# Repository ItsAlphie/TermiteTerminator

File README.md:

# Termite Terminator
For a more in-depth dive into the working and development of this project, we refer to the paper also available in this repository. Below is brief summary on how to set up the game yourself.

## The game
The player manages a coin budget and uses a spell 3 types of tangible towers to face off waves of ants attempting to pass by and eat your picknick. There is a heavy hitting tower with a long cooldown, a tower with a continuisly hitting but low damage laser and a tower that shoots as fast as the player presses its button. Additionally, there is a Freeze spell to hold enemies in place for a few seconds. The ants get increasingly stronger and come in larger groups, but the more enemies are held back, the more coins you earn for more defenses.
[🎥 Watch a demo video on YouTube](https://youtu.be/97M0W15unRk)

## Credits
Both repositories below have been used as a foundation for the python script used for the marker and gesture detection:
* OpenCV Marker Detection: https://github.com/KhairulIzwan/ArUco-markers-with-OpenCV-and-Python
* OpenCV Gesture Detection: https://github.com/kinivi/hand-gesture-recognition-mediapipe

## Setup Instruction
The following instructions are open to adjustments, if the operator deems themselves worthy and knowleadgable enough to customize the setup. But for the others, these next few sections explain how to duplicate our specific setup rather than reconfigure everything.

### Software requirements
Unity Version:
- 2022.3.49f1

python libraries: (Python 3.9 works)
- opencv-contrib-python==4.6.0.66
- imutils
- tensorflow
- mediapipe

### Wireless Connection
#### Background Information
UDP is used to communicate between the main processing computer running the Unity and camera vision, and a set of ESP8266 microcontrollers processing and controlling everything concerning the individual towers.

During the design procedure, hardcoded IP's are used to easily indentify towers and communicate with them accordingly. To set up the wireless network we rely on a mobile hotspot from a modern phone, with a preset 255.255.255.0 subnetmask.

#### Configuration
Following table shows all IP-addresses used:
Device/Service | IP | Use
--- | --- | ---
Towers | 192.168.24.TowerID | Send "b" for boosts, receive "k" and "r" to control servo
Unity (For Towers)| 192.168.24.60 | Receive "b" for boosts and identify tower, send "k" and "r" to selected towers
Unity (For Camera)| 127.0.0.1 | Unity listens to this IP, to locate and place the towers and spells within the playing field

The easiest way to set this network up on new devices is duplicate the original network. Specifically, the network name should be "Galaxy S22A88A" and its password should be "uzjw7402". It is also essential to turn off roaming and internet sevices on the mobile phone, to avoid any external DHCP server to set IP's rendering them unable to be overwritten. Next, the IP of the main computer should be set to match the one in the table above.

### Camera Vision & Towers
This part of the setup refers to the physical configuration. The fundamentals come down to a TV being laid flat on a table (projector would work, but the shadows mess with the gesture recognition) with a camera of any sort hanging above it. Ideally, the camera hangs straight above the center of the screen. 

Within Unity, more specifically in scene "Wave1" in the "LevelManager" the setup can be calibrated. Under the TowerSpawner script skewFactorX, skewFactorY, skewFactorXX, skewFactorYY and heightLimit can be adjusted to conform to the height of the camera, causing a paralax error.

As for the towers, they work on 9V batteries. So, these batteries have to be connected, after which the pins from the connector have to be put in the correct pinheader. The program on the microcontrollers should still be programmed and continue sending and receiving data as normal. As for the recognition of the towers, original aRuCo markers are used with towers ranging from 1 to 7 and the corners of the TV being 21, 22 and 23.

### Start the Game
After you managed to follow all the instruction above, you can now finally launch the game. Simply follow the next few steps to start everything up:
* launch the Unity game
* go to /TermiteTerminator/Python/Gestures/ and launch the python Camera Vision script combinedScripts.py
* make sure to place the three corner markers on your play area
* start the unity game

With this, the script should be sending all required information to the Unity game. Have fun!

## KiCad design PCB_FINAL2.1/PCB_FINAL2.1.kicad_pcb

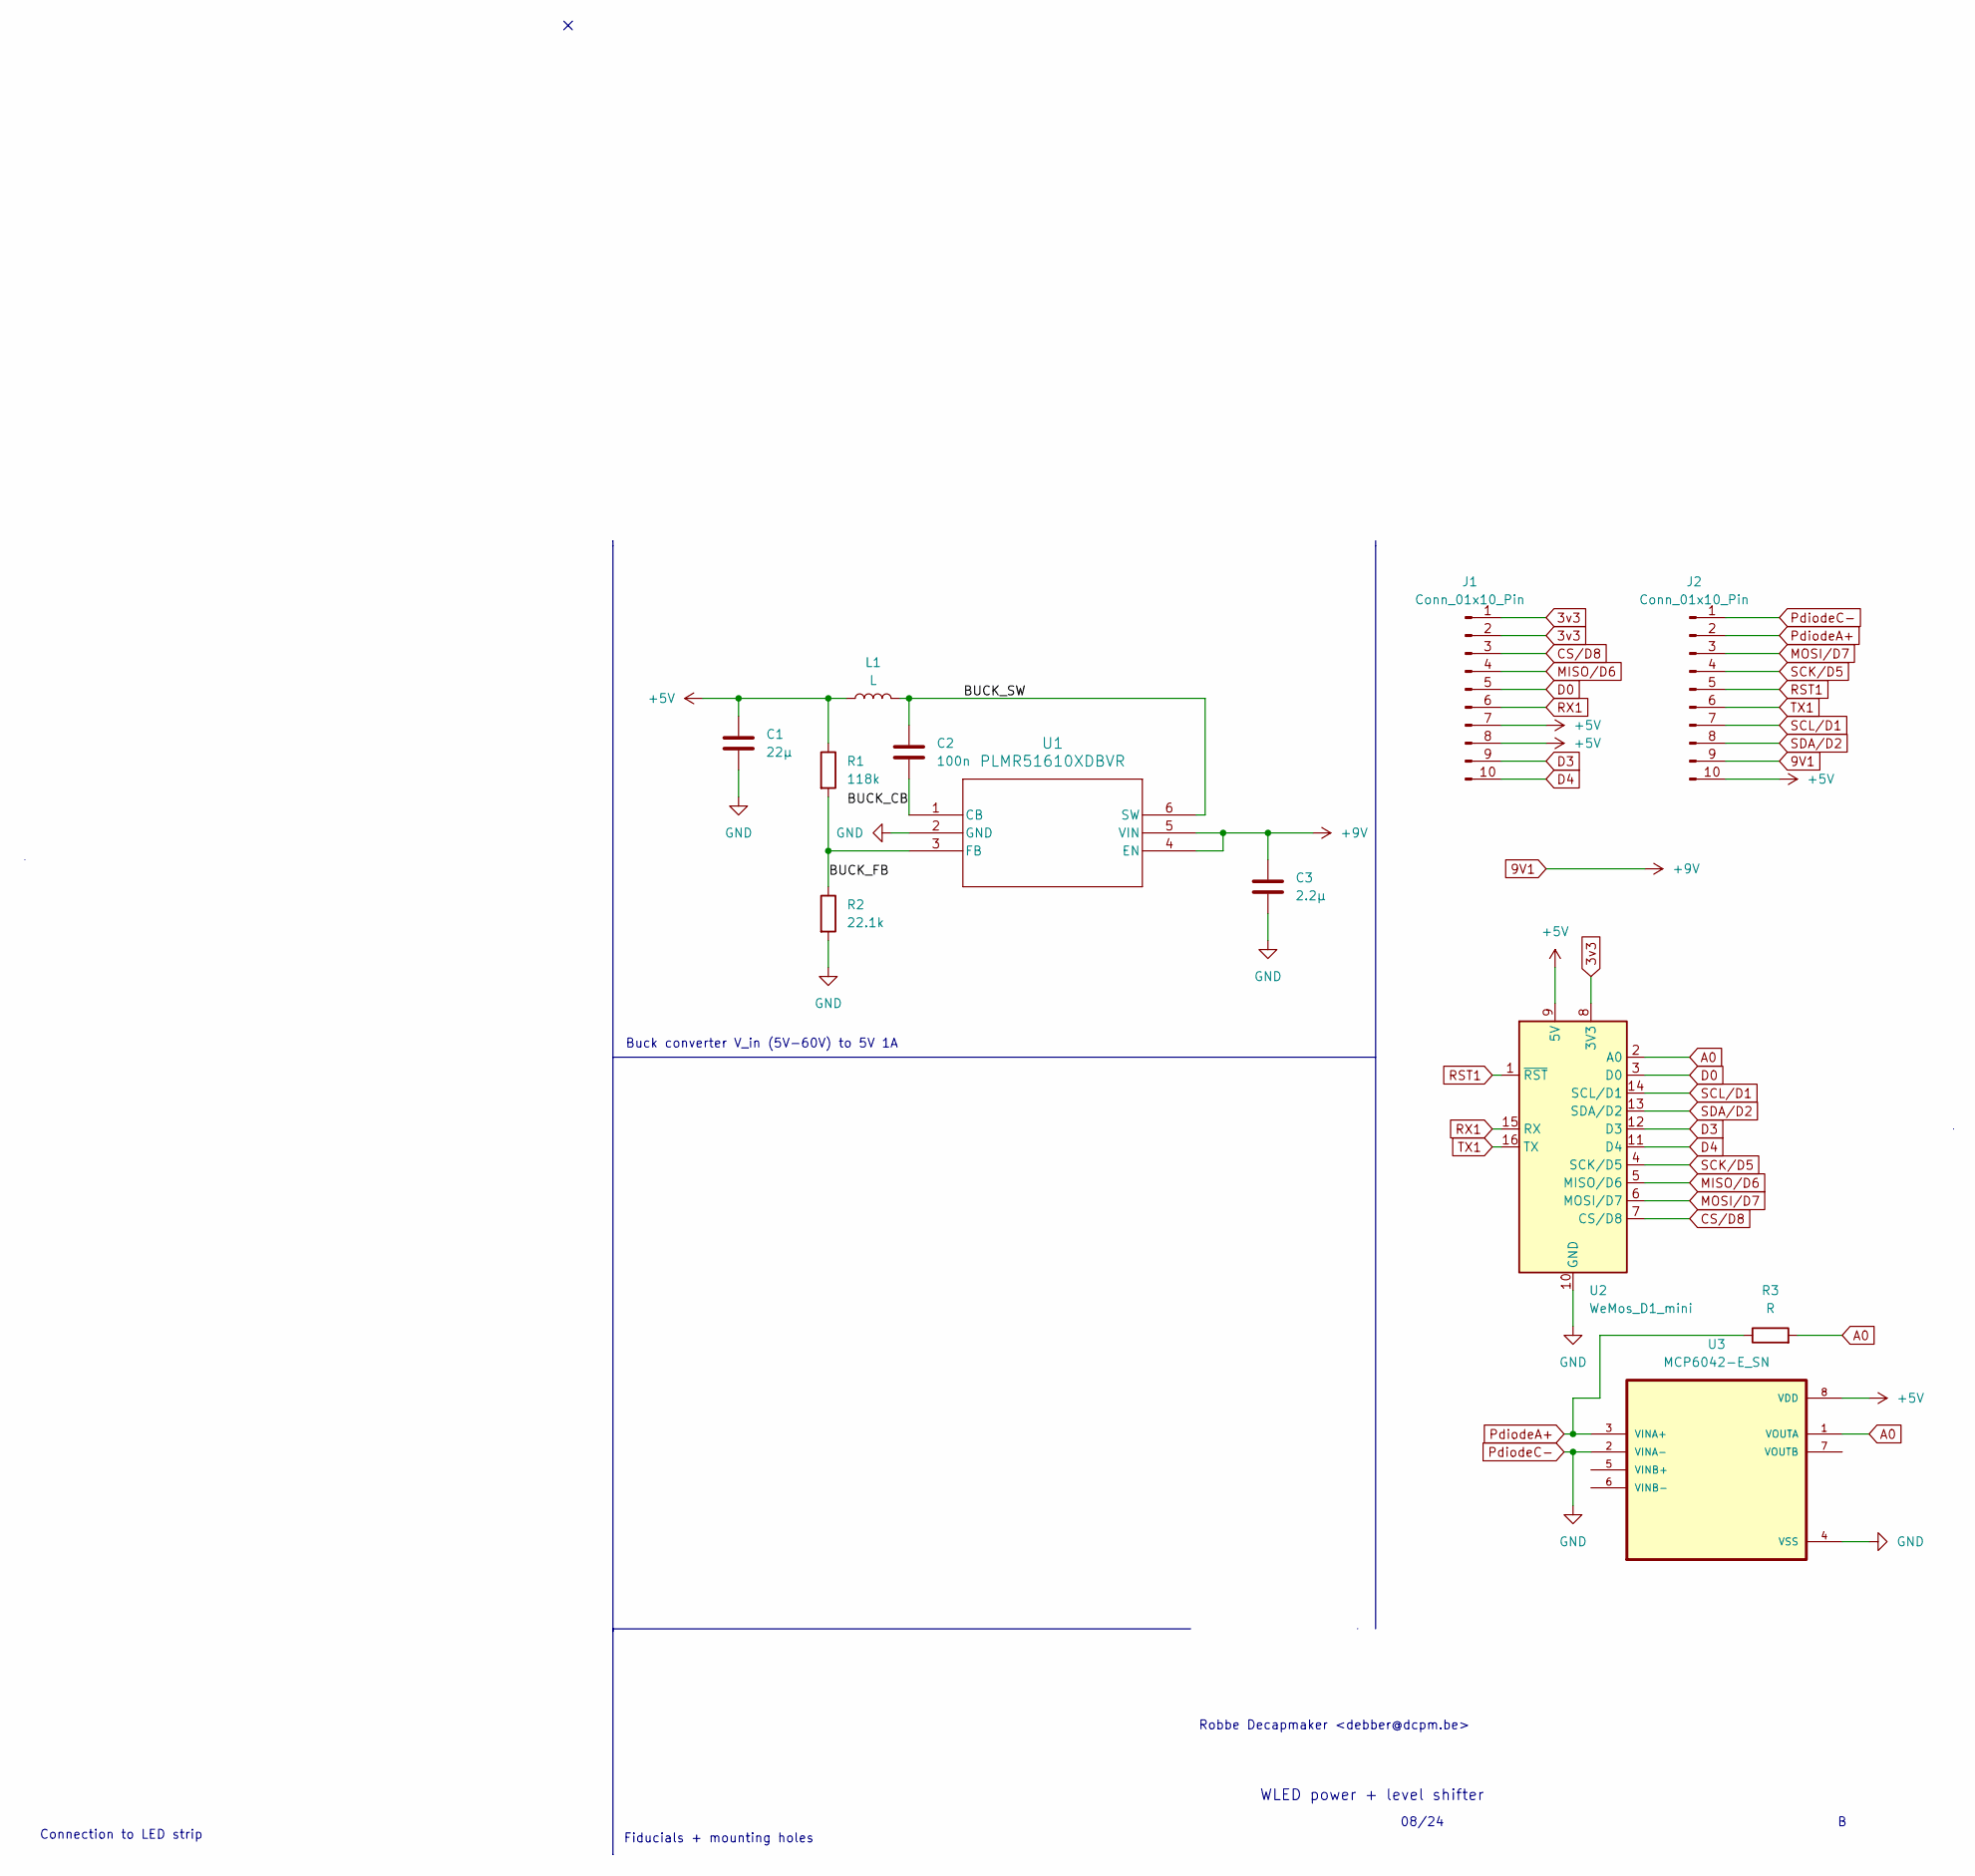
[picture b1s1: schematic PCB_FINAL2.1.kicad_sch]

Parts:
C1: 22µ; C_0805_2012Metric_Pad1.18x1.45mm_HandSolder
C2: 100n; C_0603_1608Metric_Pad1.08x0.95mm_HandSolder
C3: 2.2µ; C_0603_1608Metric_Pad1.08x0.95mm_HandSolder
J1, J2: Conn_01x10_Pin; PinSocket_1x10_P2.54mm_Vertical
L1: L; L_Bourns-SRN4018
R1: 118k; R_0603_1608Metric_Pad0.98x0.95mm_HandSolder
R2: 22.1k; R_0603_1608Metric_Pad0.98x0.95mm_HandSolder
R3: R; R_0805_2012Metric
U1: PLMR51610XDBVR; SOT-23-6_DBV_TEX
U2: WeMos_D1_mini; WEMOS_D1_mini_light
U3: MCP6042-E_SN; SOIC127P600X175-8N

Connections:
3v3: J1.1, J1.2, U2.8 (3V3)
9V1: C3.2, J2.9, U1.4 (EN), U1.5 (VIN)
+5V: C1.2, J1.7, J1.8, J2.10, L1.1, R1.1, U2.9 (5V), U3.8 (VDD)
/BUCK_CB: C2.1, U1.1 (CB)
/BUCK_FB: R1.2, R2.1, U1.3 (FB)
/BUCK_SW: C2.2, L1.2, U1.6 (SW)
A0: R3.2, U2.2 (A0), U3.1 (VOUTA)
CS/D8: J1.3, U2.7 (CS/D8)
D0: J1.5, U2.3 (D0)
D3: J1.9, U2.12 (D3)
D4: J1.10, U2.11 (D4)
MISO/D6: J1.4, U2.5 (MISO/D6)
MOSI/D7: J2.3, U2.6 (MOSI/D7)
PdiodeA+: J2.2, R3.1, U3.3 (VINA+)
PdiodeC-: C1.1, C3.1, J2.1, R2.2, U1.2 (GND), U2.10 (GND), U3.2 (VINA-), U3.4 (VSS)
RST1: J2.5, U2.1 (~RST)
RX1: J1.6, U2.15 (RX)
SCK/D5: J2.4, U2.4 (SCK/D5)
SCL/D1: J2.7, U2.14 (SCL/D1)
SDA/D2: J2.8, U2.13 (SDA/D2)
TX1: J2.6, U2.16 (TX)

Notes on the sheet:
Connection to LED strip
Fiducials + mounting holes
Robbe Decapmaker <debber@dcpm.be>
WLED power + level shifter
Buck converter V_in (5V-60V) to 5V 1A
08/24

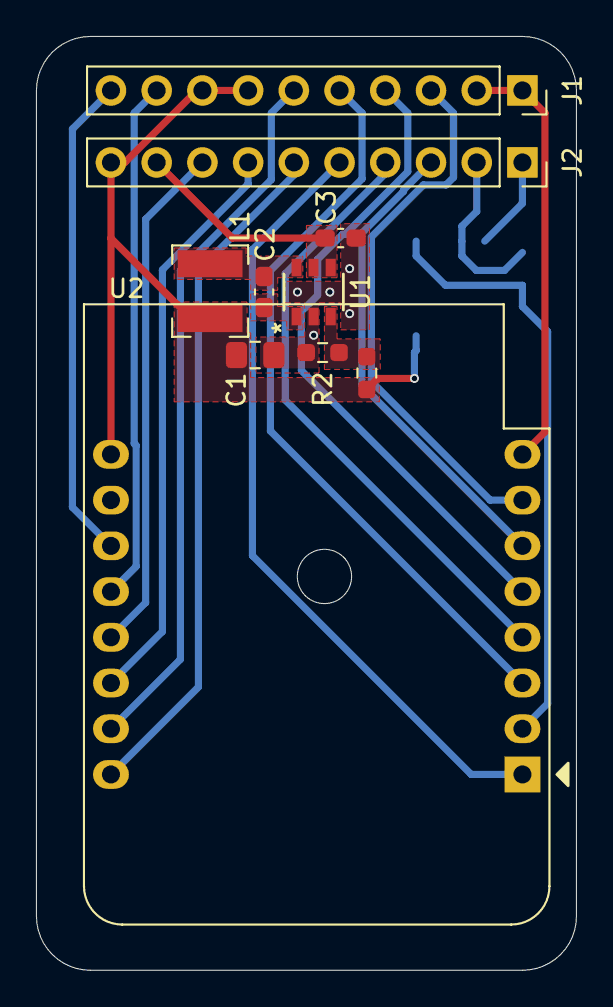
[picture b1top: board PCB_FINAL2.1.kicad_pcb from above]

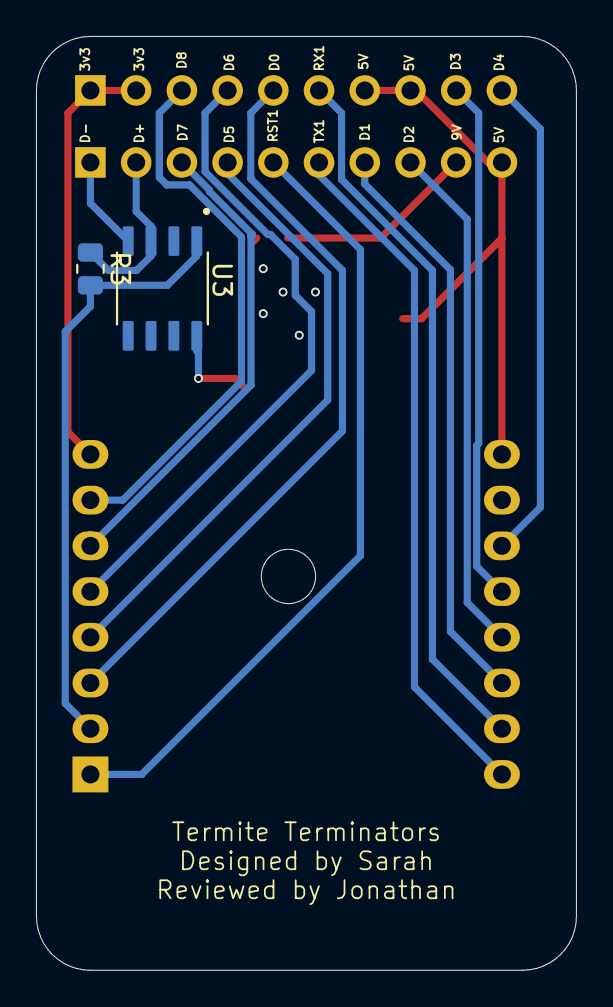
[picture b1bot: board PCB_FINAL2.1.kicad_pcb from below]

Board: 4 copper layers, 30.0 x 51.9 mm, 12 parts (2 on the bottom side), 21 nets.

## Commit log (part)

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2024-10-04 added HowToUnity.txt
2024-10-06 added .gitignore file
2024-10-06 unity project initialization
2024-10-06 Added assets and created a background
2024-10-10 added path following enemies
2024-10-10 added EnemySpawner, EnemyMovement behavior, Tower click spawn functionality
2024-10-10 added projectile behavior
2024-10-10 added health and enemy death functionality
2024-10-11 projectiles now moving through towers
2024-10-18 Moved unity project to folder
2024-10-18 Final changes for Wizard of Oz prototype and Uduino plugin
2024-10-18 moved Uduino package to Assets folder
2024-10-18 moving .gitignore within unity folder again
2024-10-18 Added Python files for basic tracking
2024-10-18 Uduino setup for wifi connection between Unity and ESP8266
2024-10-25 Added relative positioning with camera vision
2024-10-30 Added UDP cs code and test script
2024-10-31 implemented HealthControllers
2024-10-31 revision of previous enemy implementation and renaming scripts
2024-10-31 moving scripts in different folders
2024-10-31 cleaning up code, deleting unused scripts
2024-10-31 added collision matrix
2024-10-31 Adjusted UDP examples
2024-10-31 removing unused RuleTile
2024-10-31 projectile destroys itself after going out of screen
2024-10-31 added child gameobjects with spriterenderer to prefabs
2024-11-03 renamed and reorganized Animations to prepare for Animator Override Controllers
2024-11-03 renaming some fields
2024-11-03 changed Scene name to Wave1
2024-11-03 renaming animation states to more general ones
2024-11-03 Implemented BasicAnt2 animations using Override Controller
2024-11-06 Added Height Check in DetectingMarkers
2024-11-08 Added data extraction of camera vision within Unity
2024-11-08 Added TowerSpawner
2024-11-08 Added working camera vision interaction with unity
2024-11-08 Laser beam done, no collision added yet
2024-11-14 Added arduino code for Light tower, Trigger tower and Railgun tower
2024-11-15 PCB and small laserbeam adjustments
2024-11-15 GameOver logic and screen
2024-11-15 assigned correct Animator Controller to BasicAnt2
2024-11-15 initialized UI Manager
2024-11-15 added BasicAnt3
2024-11-15 small edits in BasicAnt prefabs
2024-11-15 added bomb enemy and type enemy
2024-11-15 Added Towerspawner to scene with 2 tower types
2024-11-15 turned EnemySpawnPoint into a prefab
2024-11-15 implemented Wave ScriptableObject and WaveTutorial, started reworking EnemySpawner
2024-11-15 small fix in light tower
2024-11-22 Added dynamic scaling to positioning and implemented active/inactive behaviour for out of bounds
2024-11-22 Added files for Tower Boosting
2024-11-22 Removed unnecessary marker files
2024-11-22 Edited prefabs for Tower Boosting
2024-11-22 implemented wave spawning and ending logic
2024-11-22 Applied Singleton pattern to EnemySpawner class
2024-11-22 Implemented UIManager
2024-11-22 Fixed merge errors in TowerSpawner.cs, LevelManager.cs and TypeEnemy.cs
2024-11-22 Small fix to TowerSpawner access
2024-11-22 Added railgun, base for wind tower 8)
2024-11-22 Added railgun, base for wind tower and several effects
2024-11-22 added design folder with Railgun,Trigger,Light,Barrier,Potion designs
2024-11-22 added Wind tower code for arduino
2024-11-22 Added rotation to towers and made light and rail tower visible on map
2024-11-22 added listeners to GameOver
2024-11-22 initializing Money Manager, HUD to display money
2024-11-22 implemented MoneyManager
2024-11-22 initialized ShopManager and ShopPrices, added first implementation
2024-11-24 Added Hammer stl
2024-11-27 implementing ShopManager logic
2024-11-27 implementing Inventory
2024-11-27 removed totalAmount variable
2024-11-27 Revert "removed totalAmount variable"
    This reverts commit 8372b9a8c22dc663e0d7b6632aaef2f85f64810d.
2024-11-27 Implemented receiving in CommunicationManager, updated TowerSpawner
2024-11-28 working shop system, interacts correctly with Inventory and Money
2024-11-28 added UI to display the currentMoney
2024-11-28 scene update for UI
2024-11-28 Changes to wave1 scene
2024-11-28 Fixed communication between communicationmanager and towerspawner
2024-11-28 Wind tower basics have been implemented.
2024-11-28 added graphics to money ui
2024-11-28 Added new Light tower design
2024-11-28 added juiciness
2024-11-29 small change in hierarchy
2024-11-29 set GameOverScreen to inactive again
2024-11-29 fixed double damage for enemies
2024-11-29 Changed which towers deal double damage to which enemies
2024-11-29 lighthouse tower fixed
2024-11-29 changed enemies weaknesses for demo.
2024-11-29 Further implementation of ConnectionManager and shop mechanics
2024-11-29 Added meta files for Sarah's changes
2024-11-29 Fixed KillAll() and SendMsg() for Communication to Towers
2024-11-29 Removed several print statements
2024-11-29 Added tags to tower prefabs
2024-11-29 Added new tower tags to project
2024-11-29 changed enemy sprites to make fire and bomb ant clearer
2024-11-29 copy of ShopPrices is used instead of ShopPrices
2024-11-29 Adding environmental graphics
2024-11-29 Light tower and railgun were boosted
2024-11-29 deleted meta files in wrong spot
2024-11-29 Fixed IP address of towers
2024-11-29 added 3 waves and increased ant speed
2024-11-29 added wave meta files
2024-11-29 Fixes for end game and communication
2024-11-29 updated waves
2024-11-29 Minor fix: towers couldn't move after being bought
2024-11-29 added new enemy types
2024-11-29 fixed pulse after removing type enemy
2024-11-29 Initial implementation of leaves
2024-11-29 setting environmental leaves inactive
2024-11-29 Fixed specialist enemies not having scripts.
2024-11-29 UI money feedback for adding and deducting
2024-11-30 Added updated rail gun tower, trigger tower and light tower design
2024-11-30 Fixed bug in Rail gun tower
2024-12-02 Changed 'Booster' bool to 'boosted' to make more sense
2024-12-02 Added camera calibration to towerspowner.cs
2024-12-02 Added Healing Hammer (Prefab, scrip, functionality, interaction...) + edits to Wave1 scene to accompany these changes
2024-12-03 derived class EnemyHealthController inherits Start() from base class HealthController
2024-12-03 adding HealthDisplay and logic in health controller
2024-12-03 fully implemented healthDisplay
2024-12-03 adapted more scripts to new tower states
2024-12-04 fixed definition error
2024-12-04 broken state prevents tower from shooting
2024-12-04 changed CircleCollider2D to Collider2D
2024-12-04 towers damaging other towers
2024-12-04 cleaning up comments
2024-12-04 added tower damage interaction between Railguntoweres
2024-12-05 Added gesture recognition (triangle detection)
2024-12-05 SoundController has been implemented. Certain sounds need to be implemented.
2024-12-05 collision logic in lighttower
2024-12-05 SoundFXManager
2024-12-05 fixed enemy animations to show correct sprites.
2024-12-05 Combined both camera based python script into a frankenstein .py file
2024-12-05 Lighttower sound completed WITHOUT ERRORS
2024-12-05 Add file for basic spells
2024-12-05 Changed hammer from id/ip 9 to 7
2024-12-05 added ui tower placement feedback
2024-12-05 ui tower feedback animation changes
2024-12-05 Lighttower has all the sounds implemented without bugs
2024-12-05 fixed bomb explosion placement.
2024-12-05 added FreezeSpell.cs script
2024-12-05 added singleton pattern to CommunicationController
2024-12-05 created functions in FreezeSpell script
2024-12-06 Added freeze spell effect functionality to basic enemy class, added snow effect to freeze spell.
2024-12-06 change die to public method
2024-12-06 added general die() and repair() methods
2024-12-06 Cleaned up spell scripts and changed freezespell duration to 10.
2024-12-06 fixed tagmanager file
2024-12-06 removed pathCollider object from scene
2024-12-06 pulse sound working and background music has been implemented
2024-12-06 fixed enemies not speeding back up after exiting freeze spell
2024-12-06 killing an enemy earns money
2024-12-06 prefabs with sounds
2024-12-06 Changed healing rate of hammer
2024-12-06 Made TowerSpawner a singleton and streamlined TowerHealthController and BasicTower
2024-12-06 Updated BasicSpell.cs
2024-12-06 Enabled freeze spell
2024-12-06 adding tower drop animation
2024-12-06 assigning towerFeedback gameobject in inspector
2024-12-06 adding tower drop animation to BasicTower
2024-12-06 adding towerdrop prefab to all towerse
2024-12-06 adding resetTowerFeedbackScreen
2024-12-06 adding towerFeedback when with camera detecting
2024-12-06 plays animation when buying tower fails
2024-12-06 Sound added to prefabs
2024-12-06 Changes to check lifted states
2024-12-06 correcting towerFeedbackScreen logic and adding timer
2024-12-06 triggertower works with boost
2024-12-06 removed onDamage
2024-12-06 heath display is updated through UnityEvent now
2024-12-06 Increased tower detection range of hammer
2024-12-06 Fixed issue where LevelManager would attempt to repair and kill HealingHammer
2024-12-12 adding draft of the paper
2024-12-12 Updated camera calibration and added cooldown to spell usage
2024-12-12 Updated healing hammer prefab (smaller and red cross)
2024-12-12 Updated way of lift detection in python script
2024-12-12 Minor change in BasicTower script
2024-12-12 added Coin pop-up animation
2024-12-12 decluttering the code and removing log messages
2024-12-12 Removing even more print statements
2024-12-12 CoinPopUp animation plays when enemy dies
2024-12-12 cleaning up more code
2024-12-12 Sarah's sound changes
2024-12-12 Adjustments to calibration
2024-12-12 Updated spells to cost money and be included in the UI
2024-12-12 Added sprite for freeze spell UI
2024-12-12 Externalised heightdetection to unity and slowed scan rate
2024-12-12 Sarah's changes to audio
2024-12-12 Bug fix: towers would sell at the start of a game
2024-12-12 Changes to scene wave1
2024-12-12 added PathCollider as a child object
2024-12-12 new buy failed UnityEvent
2024-12-12 Highscore table implemented. Pointcontroller being able to update the highscore table
2024-12-12 adding some debugs for path colission
2024-12-12 Implemented waves succeeding eachother and added text in between waves.
2024-12-12 sound plays when buying fails
2024-12-12 fixed failed tower bought feedback
2024-12-12 Created wave1 2 which contains waves configured correctly.
2024-12-12 added delay in not bought feedback
2024-12-13 changed HUD placement
2024-12-13 setting health on 0 when tower dies
2024-12-13 added path collision to all towers
2024-12-13 enabled isTrigger
2024-12-13 Bug fix in height detection
2024-12-13 Calibration changes to wave1 scene
2024-12-13 changing the popup ONCE AGAIN
2024-12-13 reworked popup again
2024-12-13 updated Wave1 scene to include consecutive waves.
2024-12-13 Returned wavetutorial to correct ants.
2024-12-13 UI changes to spell
2024-12-13 Changes to freeze prefab and prices
2024-12-13 Restructured lighthouse boost
2024-12-16 leaderboard is initialized
2024-12-17 Added Hints to Towers and spell
2024-12-17 Bug fix: Now checking all hands in for gesture detection
2024-12-17 fully functioning highscore table, only need to transfer score to different classes
2024-12-17 Highscore table fully implemented. Scores can be saved from the playerscore, UI needs to be changed :(
2024-12-18 removing unused variable
2024-12-18 cleaning Debug.Logs
2024-12-18 adjusting bomb animation
2024-12-18 basicTower shoots automatically again
2024-12-18 Sound added to bomb and tower being hit. Should be playable
2024-12-18 added feedback coinPopUp to tower buying
2024-12-19 Highscore board implemented in the scenery
2024-12-19 Added tower damaged and downed hints
2024-12-19 Implemented ants having hats which shrink as they take damage.
2024-12-19 Sound is less loud
2024-12-19 Lighttower should be fixed
2024-12-19 Changes tijdens testen dag voor de deadline
2024-12-19 Added wave 4 and 5 to scene 1
2025-01-11 Added Final Version of Paper
2025-01-11 Removed old paper
2025-09-29 Update README.md with demo video
2025-10-31 Leaderboard bug fix
2025-10-31 decluttering console from irrelevant log messages
2025-10-31 re-enable tower communication and updated scene
